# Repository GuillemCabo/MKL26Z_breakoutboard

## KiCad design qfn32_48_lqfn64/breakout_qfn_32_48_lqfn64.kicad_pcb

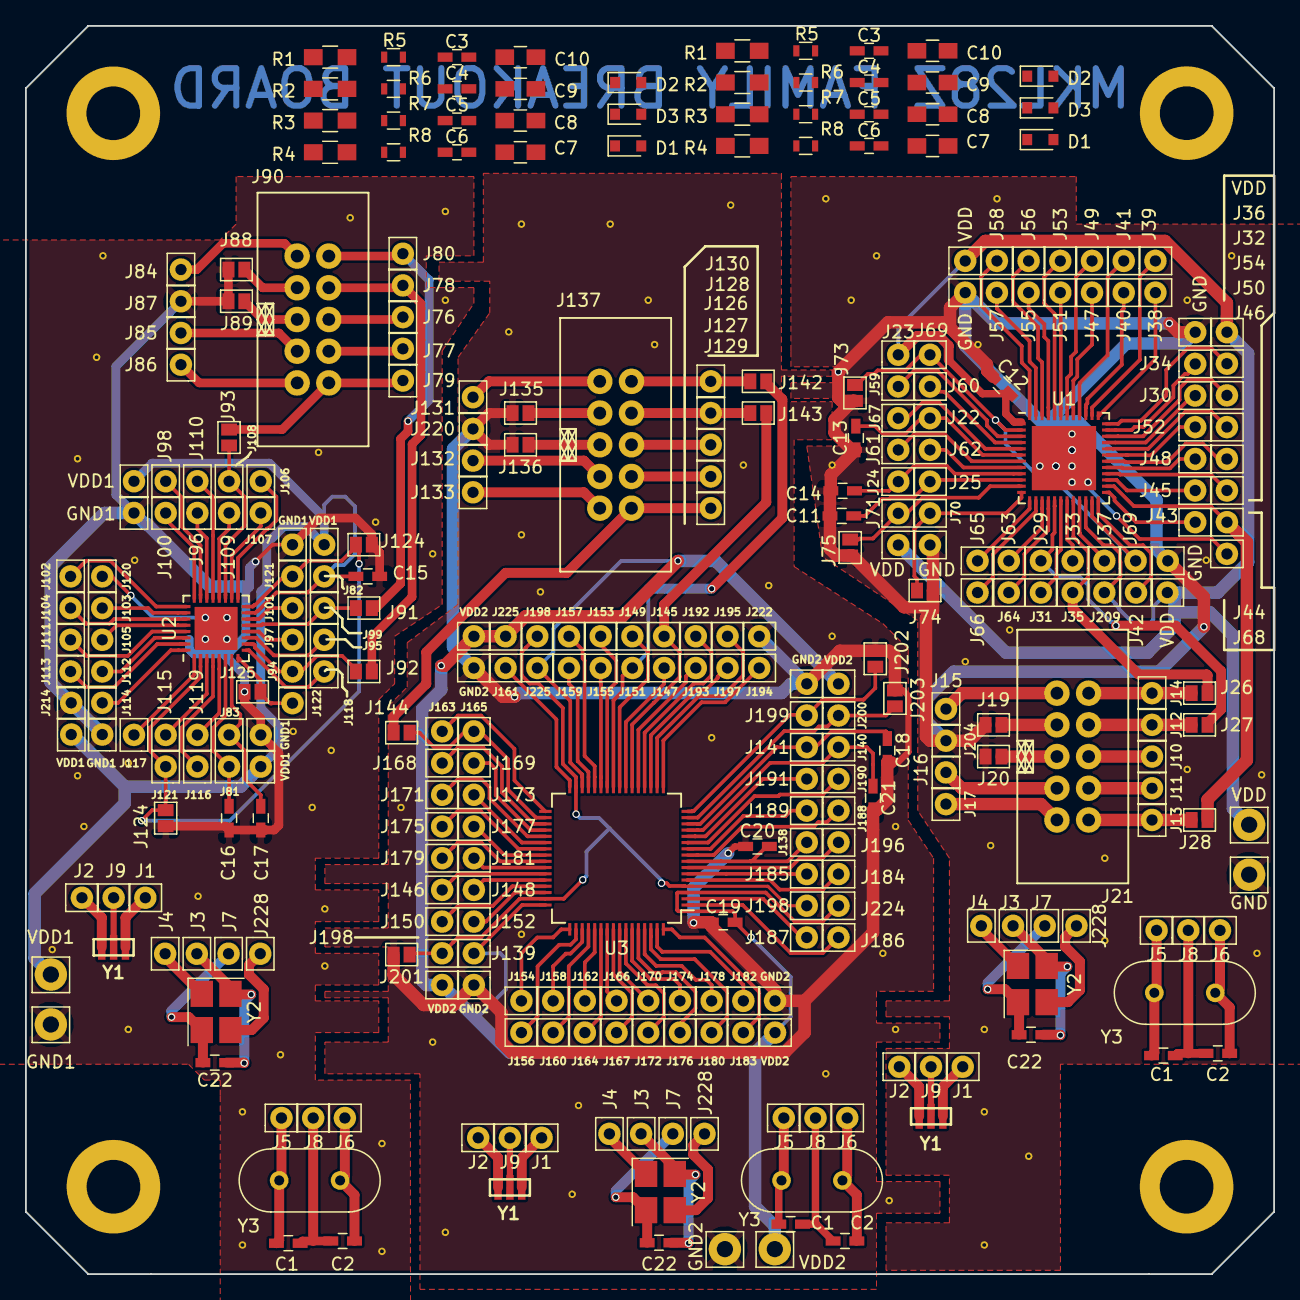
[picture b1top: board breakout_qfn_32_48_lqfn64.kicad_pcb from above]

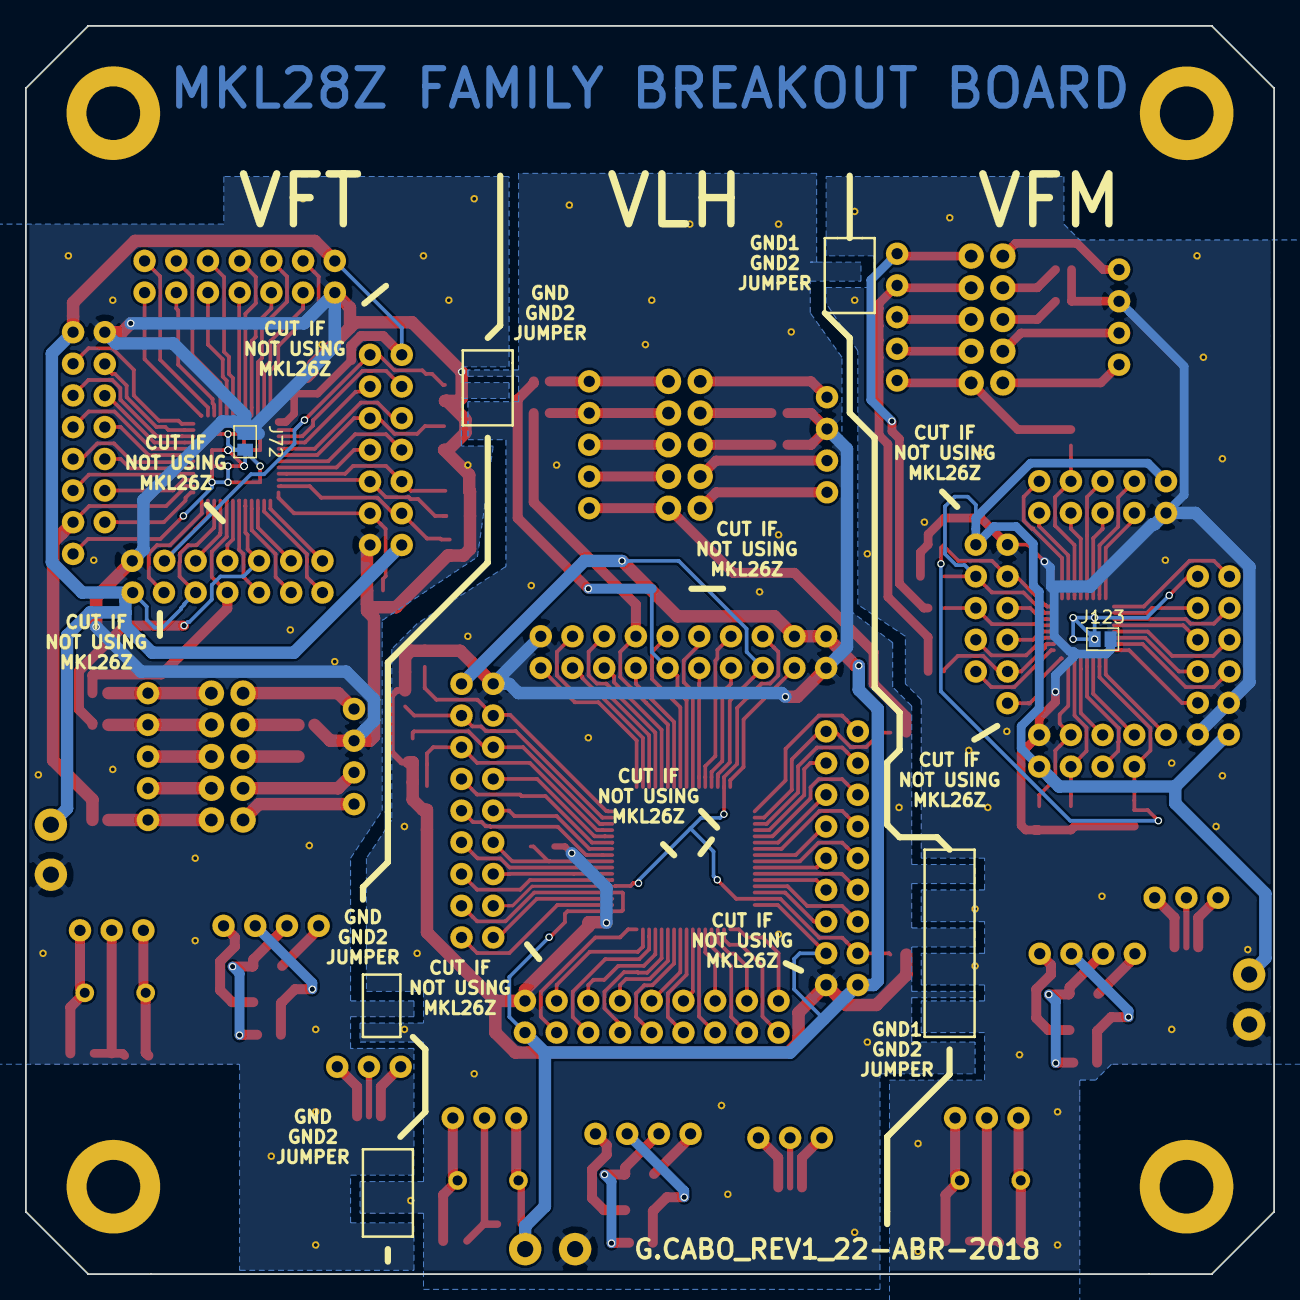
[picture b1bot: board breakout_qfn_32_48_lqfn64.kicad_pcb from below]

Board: 2 copper layers, 100.0 x 100.0 mm, 335 parts (2 on the bottom side), 182 nets.

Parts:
C1, C1#2, C1#3, C2, C2#2, C2#3, C3, C3#2, C4, C4#2, C5, C5#2, C6, C6#2, C11, C12, C13, C14, C15, C16, C17, C18, C19, C20, C21, C22, C22#2, C22#3: C; C_0603_HandSoldering
C7, C7#2, C8, C8#2, C9, C9#2, C10, C10#2: C; C_0805_HandSoldering
D1, D1#2, D2, D2#2, D3, D3#2: D; D_0805
GND, GND1#5, GND2: Pin_d1.4mm_L8.5mm_W2.8mm_FlatFork
GND1, GND1#2, GND1#3, GND1#4, GND2#2, GND2#3, GND2#4, GND2#5: TEST_1P; Pin_d0.9mm_L10.0mm_W2.4mm_FlatFork
GND#2, GND#3, GND#4, GND#5: TEST_1P; Pin_d0.9mm_L10.0mm_W2.4mm_FlatFork
J1, J1#2, J1#3, J2, J2#2, J2#3, J3, J3#2, J3#3, J4, J4#2, J4#3, J5, J5#2, J5#3, J6, J6#2, J6#3, J7, J7#2, J7#3, J8, J8#2, J8#3, J9, J9#2, J9#3, J10, J11, J12, J13, J14, J15, J16, J17, J22, J23, J24, J25, J29, J30, J31, J32, J33, J34, J35, J36, J37, J38, J39, J40, J41, J42, J43, J44, J45, J46, J47, J48, J49, J50, J51, J52, J53, J54, J55, J56, J57, J58, J59, J60, J61, J62, J63, J64, J65, J66, J67, J68, J69, J69#2, J70, J71, J76, J77, J78, J79, J80, J81, J82, J83, J84, J85, J86, J87, J94, J95, J96, J97, J98, J99, J100, J101, J102, J103, J104, J105, J106, J107, J108, J109, J110, J111, J112, J113, J114, J115, J116, J117, J118, J119, J120, J121, J121#2, J122, J126, J127, J128, J129, J130, J131, J132, J133, J138, J139, J140, J141, J145, J146, J147, J148, J149, J150, J151, J152, J153, J154, J155, J156, J157, J158, J159, J160, J161, J162, J163, J164, J165, J166, J167, J168, J169, J170, J171, J172, J173, J174, J175, J176, J177, J178, J179, J180, J181, J182, J183, J184, J185, J186, J187, J188, J189, J190, J191, J192, J193, J194, J195, J196, J197, J198, J198#2, J198#3, J199, J200, J204, J209, J214, J220, J222, J224, J225, J225#2, J228, J228#2, J228#3: TEST_1P; Pin_d0.9mm_L10.0mm_W2.4mm_FlatFork
J19, J20, J26, J27, J28, J72, J73, J74, J75, J88, J89, J91, J92, J93, J123, J124, J124#2, J125, J135, J136, J142, J143, J144, J201, J202, J203: TEST_2P; GS2
J21, J90, J137: CONN_02X05; 70246-1004 MOLEX 10 PIN
R1, R1#2, R2, R2#2, R3, R3#2, R4, R4#2: R; R_0805_HandSoldering
R5, R5#2, R6, R6#2, R7, R7#2, R8, R8#2: R; R_0603
U1: MKL26Z64VFT4; QFN-48-1EP_7x7mm_Pitch0.5mm
U2: MKL26Z64VFM4; QFN-32-1EP_5x5mm_Pitch0.5mm
U3: MKL26Z64VLH4; LQFP-64_10x10mm_Pitch0.5mm
VDD, VDD1, VDD2: Pin_d1.4mm_L8.5mm_W2.8mm_FlatFork
VDD1#2, VDD1#3, VDD1#4, VDD1#5, VDD2#2, VDD2#3, VDD2#4, VDD2#5: TEST_1P; Pin_d0.9mm_L10.0mm_W2.4mm_FlatFork
VDD#2, VDD#3, VDD#4, VDD#5: TEST_1P; Pin_d0.9mm_L10.0mm_W2.4mm_FlatFork
Y1, Y1#2, Y1#3: Crystal_GND2; murata cstce16mov53
Y2, Y2#2, Y2#3: Crystal_GND23; Crystal_SMD_TXC_7M-4pin_3.2x2.5mm_HandSoldering
Y3, Y3#2, Y3#3: Crystal; Crystal_HC49-U_Vertical

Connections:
GND: C11.2, C12.1, C13.1, C14.2, GND.1, GND#2.1, GND#3.1, GND#4.1, GND#5.1, J19.2, J20.2, J72.2, J73.2, J74.2, J75.2, J204.1
GND1: C15.1, C16.1, C17.2, GND1.1, GND1#2.1, GND1#3.1, GND1#4.1, GND1#5.1, J87.1, J88.2, J89.2, J123.2, J124.2, J124#2.2, J125.2, J214.1
GND2: C18.2, C19.1, C20.1, C21.2, GND2.1, GND2#2.1, GND2#3.1, GND2#4.1, GND2#5.1, J135.2, J136.2, J201.2, J202.2, J203.2, J220.1, J222.1
GNDDETECT: J17.1, J21.9
GNDDETECT1: J86.1, J90.9
GNDDETECT2: J133.1, J137.9
KEY: J16.1, J21.7
KEY1: J85.1, J90.7
KEY2: J132.1, J137.7
NC: J11.1, J21.8
NC1: J77.1, J90.8
NC2: J127.1, J137.8
NRESET: J13.1, J21.10, J28.2
NRESET1: J79.1, J90.10, J93.2
NRESET2: J129.1, J137.10, J144.2
unnamed: C1.1, C1#2.1, C1#3.1, J5.1, J5#2.1, J5#3.1, Y3.1, Y3#2.1, Y3#3.1
unnamed: C1.2, C1#2.2, C1#3.2, C2.2, C2#2.2, C2#3.2, J8.1, J8#2.1, J8#3.1
unnamed: C2.1, C2#2.1, C2#3.1, J6.1, J6#2.1, J6#3.1, Y3.2, Y3#2.2, Y3#3.2
unnamed: C11.1, J25.1, U1.10
unnamed: C13.2, J22.1, U1.6
unnamed: C14.1, J24.1, U1.9
unnamed: C16.2, J81.1, U2.6
unnamed: C17.1, J83.1, U2.7
unnamed: C18.1, J141.1, U3.14
unnamed: C20.2, J138.1, U3.8
unnamed: C21.1, J140.1, U3.13
unnamed: C22.1, C22#2.1, C22#3.1, J7.1, J7#2.1, J7#3.1, Y2.2, Y2#2.2, Y2#3.2
unnamed: C22.2, C22#2.2, C22#3.2, J3.1, J3#2.1, J3#3.1, Y2.4, Y2#2.4, Y2#3.4
unnamed: J1.1, J1#2.1, J1#3.1, Y1.3, Y1#2.3, Y1#3.3
unnamed: J2.1, J2#2.1, J2#3.1, Y1.1, Y1#2.1, Y1#3.1
unnamed: J4.1, J4#2.1, J4#3.1, Y2.1, Y2#2.1, Y2#3.1
unnamed: J9.1, J9#2.1, J9#3.1, Y1.2, Y1#2.2, Y1#3.2
unnamed: J19.1, J21.3
unnamed: J20.1, J21.5
unnamed: J26.1, J35.1, U1.20
unnamed: J27.1, J29.1, U1.17
unnamed: J28.1, J44.1, U1.26
unnamed: J30.1, U1.33
unnamed: J31.1, U1.18
unnamed: J32.1, U1.34
unnamed: J33.1, U1.19
unnamed: J34.1, U1.35
unnamed: J36.1, U1.36
unnamed: J37.1, U1.21
unnamed: J38.1, U1.37
unnamed: J39.1, U1.38
unnamed: J40.1, U1.39
unnamed: J41.1, U1.40
unnamed: J42.1, U1.24
unnamed: J43.1, U1.25
unnamed: J45.1, U1.27
unnamed: J46.1, U1.28
unnamed: J47.1, U1.41
unnamed: J48.1, U1.29
unnamed: J49.1, U1.42
unnamed: J50.1, U1.30
unnamed: J51.1, U1.43
unnamed: J52.1, U1.31
unnamed: J53.1, U1.44
unnamed: J54.1, U1.32
unnamed: J55.1, U1.45
unnamed: J56.1, U1.46
unnamed: J57.1, U1.47
unnamed: J58.1, U1.48
unnamed: J59.1, U1.3
unnamed: J60.1, U1.4
unnamed: J61.1, U1.7
unnamed: J62.1, U1.8
unnamed: J63.1, U1.15
unnamed: J64.1, U1.16
unnamed: J65.1, U1.13
unnamed: J66.1, U1.14
unnamed: J67.1, U1.5
unnamed: J68.1, J72.1, U1.49
unnamed: J69.1, J69#2.1, J73.1, U1.2, U1.23
unnamed: J70.1, J74.1, U1.12
unnamed: J71.1, J75.1, U1.11
unnamed: J88.1, J90.3
unnamed: J89.1, J90.5
unnamed: J91.1, J99.1, U2.13
unnamed: J92.1, J94.1, U2.10
unnamed: J95.1, U2.11
unnamed: J96.1, U2.22
unnamed: J97.1, U2.12
unnamed: J98.1, U2.23
unnamed: J100.1, U2.24
unnamed: J101.1, U2.14
unnamed: J102.1, U2.25
unnamed: J103.1, U2.26
unnamed: J104.1, U2.27
unnamed: J105.1, U2.28
unnamed: J106.1, U2.17
unnamed: J107.1, U2.18
unnamed: J93.1, J108.1, U2.19
unnamed: J109.1, U2.20
unnamed: J110.1, U2.21
unnamed: J111.1, U2.29
unnamed: J112.1, U2.30
unnamed: J113.1, U2.31
unnamed: J114.1, U2.32
unnamed: J115.1, U2.3
unnamed: J116.1, U2.4
unnamed: J117.1, U2.1
unnamed: J118.1, U2.9
unnamed: J119.1, U2.5
unnamed: J120.1, J123.1, U2.33
unnamed: J121.1, J121#2.1, J124.1, J124#2.1, U2.2, U2.16
unnamed: J122.1, J125.1, U2.8
unnamed: J135.1, J137.3
unnamed: J136.1, J137.5
unnamed: J142.1, J151.1, U3.25
unnamed: J143.1, J145.1, U3.22
unnamed: J144.1, J165.1, U3.34
unnamed: J146.1, U3.43
unnamed: J147.1, U3.23
unnamed: J148.1, U3.44
unnamed: J149.1, U3.24
unnamed: J150.1, U3.45
unnamed: J152.1, U3.46
unnamed: J153.1, U3.26
unnamed: J154.1, U3.49
unnamed: J155.1, U3.27
unnamed: J156.1, U3.50
unnamed: J157.1, U3.28
unnamed: J158.1, U3.51
unnamed: J159.1, U3.29
unnamed: J160.1, U3.52
unnamed: J161.1, U3.32
unnamed: J162.1, U3.53
unnamed: J163.1, U3.33
unnamed: J164.1, U3.54
unnamed: J166.1, U3.55
unnamed: J167.1, U3.56
unnamed: J168.1, U3.35
unnamed: J169.1, U3.36
unnamed: J170.1, U3.57
unnamed: J171.1, U3.37
unnamed: J172.1, U3.58
unnamed: J173.1, U3.38
unnamed: J174.1, U3.59
unnamed: J175.1, U3.39
unnamed: J176.1, U3.60
unnamed: J177.1, U3.40
unnamed: J178.1, U3.61
unnamed: J179.1, U3.41
unnamed: J180.1, U3.62
unnamed: J181.1, U3.42
unnamed: J182.1, U3.63
unnamed: J183.1, U3.64
unnamed: J184.1, U3.5
unnamed: J185.1, U3.6
unnamed: J186.1, U3.1
unnamed: J187.1, U3.2
unnamed: J188.1, U3.9
unnamed: J189.1, U3.10
unnamed: J190.1, U3.11
unnamed: J191.1, U3.12
unnamed: J192.1, U3.20
unnamed: J193.1, U3.21
unnamed: J194.1, U3.17
unnamed: J195.1, U3.18
unnamed: J196.1, U3.7
unnamed: J197.1, U3.19
unnamed: J198.1, J198#2.1, J198#3.1, J201.1, U3.4, U3.31, U3.47
unnamed: J199.1, J202.1, U3.16
unnamed: J200.1, J203.1, U3.15
unnamed: J228.1, J228#2.1, J228#3.1, Y2.3, Y2#2.3, Y2#3.3
SWDCLK: J12.1, J21.4, J27.2
SWDCLK1: J78.1, J90.4, J92.2
SWDCLK2: J128.1, J137.4, J143.2
SWDIO: J14.1, J21.2, J26.2
SWDIO1: J80.1, J90.2, J91.2
SWDIO2: J130.1, J137.2, J142.2
SWO: J10.1, J21.6
SWO1: J76.1, J90.6
SWO2: J126.1, J137.6
VDD: C12.2, J23.1, J209.1, U1.1, U1.22, VDD.1, VDD#2.1, VDD#3.1, VDD#4.1, VDD#5.1
VDD1: C15.2, J82.1, U2.15, VDD1.1, VDD1#2.1, VDD1#3.1, VDD1#4.1, VDD1#5.1
VDD2: C19.2, J139.1, J224.1, J225.1, J225#2.1, U3.3, U3.30, U3.48, VDD2.1, VDD2#2.1, VDD2#3.1, VDD2#4.1, VDD2#5.1
VTREF: J15.1, J21.1
VTREF1: J84.1, J90.1
VTREF2: J131.1, J137.1

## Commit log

2018-04-23 ejemplo usando git
2018-04-23 removed backups
2018-04-23 first update of the files. PCB sent to production
2018-04-23 errata on name MKL28 instead of mkl26
